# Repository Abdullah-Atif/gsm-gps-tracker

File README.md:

# GSM/GPS Live Vehicle Tracker

**ESP32 / ESP32-C3 + NEO-M8N GPS + SIM800L (2G) → MQTT → live web map**

A low-cost live tracker for cars, bikes and EV three-wheelers. The device reads its position from a NEO-M8N GPS module and sends it over 2G GPRS (SIM800L) every 5 seconds. A static web page shows it live on a map.

The whole system runs with **no server, no PC and no paid service**:

- The device publishes to a free public MQTT broker.
- The map page is a single HTML file on GitHub Pages.
- It subscribes to the same broker over a secure WebSocket.

**Live map:** <https://abdullah-atif.github.io/gps-tracker/#key=YOUR_TRACKER_KEY>

Author: **Abdullah Atif**, Department of EEE, BUET.

---

## Contents

- [How it works](#how-it-works)
- [Hardware](#hardware)
- [Repository layout](#repository-layout)
- [Quick start](#quick-start)
- [Wiring](#wiring)
- [Carrier PCBs](#carrier-pcbs)
- [Data format](#data-format)
- [Design decisions](#design-decisions)
- [Troubleshooting](#troubleshooting)
- [Project status](#project-status)
- [Security note](#security-note)
- [License](#license)

---

## How it works

```mermaid
flowchart LR
    GPS["NEO-M8N GPS<br/>NMEA @ 9600 baud"] -->|UART| MCU["ESP32 / ESP32-C3<br/>TinyGPSPlus parser"]
    MCU -->|"UART + AT commands<br/>(TinyGSM)"| GSM["SIM800L<br/>2G GPRS"]
    GSM -->|"MQTT over TCP :1883<br/>(PubSubClient)"| BROKER[("broker.emqx.io<br/>free public MQTT broker")]
    BROKER -->|"MQTT over WebSocket<br/>wss :8084"| WEB["Web map (GitHub Pages)<br/>Leaflet + OpenStreetMap + MQTT.js"]
    WEB --> USER(["Any phone or PC browser"])
```

1. **Read the position.** The ESP32 parses NMEA sentences from the GPS: position, speed, course, altitude, satellites and HDOP.
2. **Connect.** The SIM800L brings up GPRS. Then the ESP32 opens an MQTT connection on plain TCP port 1883. The SIM800L's built-in TLS is too old for modern servers, so plain MQTT is the reliable choice.
3. **Publish.** Every 5 s the device publishes a JSON message as a **retained** message. A page opened later still shows the last known position immediately.
4. **Online/offline status.** The device registers an MQTT **Last Will** (`offline`). If the device loses power or network, the broker publishes it automatically, and the map shows the tracker as offline.
5. **Show the map.** The web page subscribes to `gpstrk/<TRACKER_KEY>/+/loc` and `/status`. It:
   - draws a heading arrow for each device
   - keeps a trail in the browser
   - shows speed, satellites, HDOP and battery voltage.

---

## Hardware

| Part | Notes |
|---|---|
| ESP32 DOIT DevKit V1 (30-pin) **or** ESP32-C3 Super Mini | The DevKit version is tested end to end. The C3 version is a smaller board. |
| NEO-M8N GPS module + patch antenna | 9600 baud default. The antenna must see the sky. |
| SIM800L mini module + antenna | 2G only. Needs a SIM with a data plan and 2G coverage. |
| 1S Li-ion cell (18650 / LiPo, protected) | Powers the SIM800L directly (3.4–4.4 V). |
| MT3608 boost module | 1S cell → 5.0 V for the ESP32 and GPS. |
| 1000 µF + 100 nF capacitors | Next to SIM800L VCC, to absorb the 2 A transmit bursts. |
| 10 kΩ + 20 kΩ resistors | Level divider: ESP32 TX (3.3 V) → SIM800L RXD (2.8 V logic). |
| Slide switch, JST-XH connector | Power switch and battery plug. |

---

## Repository layout

```
gsm-gps-tracker/
├── esp32_devkit/                ESP32 DevKit V1 version (tested)
│   ├── gps_test/                  GPS check with baud-rate auto-detect
│   ├── sim800l_test/              7 PASS/FAIL checks: power, SIM, signal, GPRS, broker TCP
│   ├── sim800l_autodetect/        finds TX/RX orientation + baud, saves 9600 baud in the modem
│   ├── mqtt_sim800l_tracker/      THE TRACKER (2G GPRS)
│   ├── mqtt_wifi_tracker/         same tracker over Wi-Fi / phone hotspot (with network diagnostics)
│   └── pcb/                       KiCad carrier board (60 x 52 mm), Gerbers, BOM, generator
├── esp32c3_supermini/           ESP32-C3 Super Mini version
│   ├── c3_gps_test/
│   ├── c3_sim800l_autodetect/
│   ├── c3_mqtt_sim800l_tracker/   tracker + battery voltage report
│   ├── c3_wiring_diagram.png/.svg full wiring diagram
│   ├── c3_supermini_pinout.png    top/bottom pinout of the Super Mini
│   └── pcb/                       KiCad carrier board v2 (53 x 52 mm), all modules plug in
├── web/index.html               live map page (single file, no build step)
├── LICENSE
└── README.md
```

Each PCB folder has its own README with ordering and assembly notes.

---

## Quick start

### 1. Arduino IDE

1. Install the **esp32 by Espressif Systems** board package.
2. Install these libraries from Library Manager:

| Library | Author |
|---|---|
| TinyGPSPlus | Mikal Hart |
| TinyGSM | Volodymyr Shymanskyy |
| PubSubClient | Nick O'Leary |

3. Pick the board settings:

| Version | Board | Extra setting |
|---|---|---|
| DevKit | **ESP32 Dev Module** | - |
| C3 Super Mini | **ESP32C3 Dev Module** | **Tools → USB CDC On Boot → Enabled** (required for the Serial Monitor) |

### 2. Run the sketches in order

| Step | DevKit sketch | C3 sketch | What to look for |
|---|---|---|---|
| 1 | `gps_test` | `c3_gps_test` | Satellites > 0 and a fix outdoors (first fix can take 1–5 min) |
| 2 | `sim800l_test` | - | All 7 checks PASS |
| 2b | `sim800l_autodetect` | `c3_sim800l_autodetect` | `FOUND` with the right TX/RX orientation; modem saved at 9600 baud |
| 3 | `mqtt_sim800l_tracker` | `c3_mqtt_sim800l_tracker` | `published` lines in the Serial Monitor |

### 3. Configure the tracker

At the top of the tracker sketch:

```cpp
const char APN[]         = "gpinternet";             // Grameenphone; Robi/Airtel "internet", Banglalink "blweb"
const char* TRACKER_KEY  = "change-this-secret-key"; // long random text, also used in the map link
const char* DEVICE_ID    = "car-01";                 // one ID per vehicle
```

### 4. Open the map

```
https://abdullah-atif.github.io/gps-tracker/#key=YOUR_TRACKER_KEY
```

You can also open `web/index.html` from disk or host it yourself. Anyone with the link, key included, can watch the tracker. Several devices with the same key appear on the same map.

---

## Wiring

### ESP32-C3 Super Mini

| ESP32-C3 pin | Connects to | Firmware define |
|---|---|---|
| 5V | MT3608 OUT+ (5.0 V) | - |
| GND | common GND | - |
| GPIO4 | SIM800L TXD | `MODEM_RX_PIN 4` |
| GPIO3 | 10 kΩ → SIM800L RXD (20 kΩ from RXD to GND) | `MODEM_TX_PIN 3` |
| GPIO2 | SIM800L RST | `MODEM_RST_PIN 2` |
| GPIO1 | GPS TX | `GPS_RX_PIN 1` |
| GPIO0 | GPS RX | `GPS_TX_PIN 0` |
| GPIO8 | on-board LED (active LOW), blinks on each publish | `LED_PIN 8` |

> The Super Mini's pin labels are printed on its **underside**. Seen from the top (chip side up, USB-C up), the 5V / GND / 3V3 / GPIO4..0 row is on the **right**. See [`c3_supermini_pinout.png`](esp32c3_supermini/c3_supermini_pinout.png).

### ESP32 DevKit V1

| ESP32 pin | Connects to | Notes |
|---|---|---|
| GPIO16 (RX2) | GPS TX | |
| GPIO17 (TX2) | GPS RX | |
| VIN (5 V) | GPS VCC | from the MT3608 5.0 V output |
| GPIO26 | SIM800L TXD | direct |
| GPIO27 | SIM800L RXD | through the 10k/20k divider |
| GPIO5 | SIM800L RST | optional |
| GND | common GND | |

### Power (both versions)

```
1S Li-ion ─ switch ─ VBAT ─┬─ SIM800L VCC   (1000 µF + 100 nF right at the module)
                           └─ MT3608 IN+ ─ 5.0 V ─┬─ ESP32 5V / VIN  (100 µF)
                                                  └─ GPS VCC
```

- **Never power the SIM800L from the ESP32's 3.3 V or 5 V pin.** It draws up to 2 A in short bursts.
- **Set the MT3608 to 5.0 V with a multimeter before connecting anything.** New modules often ship at 12 V or more.
- The C3 Super Mini has no protection between USB 5 V and its 5V pin. Switch the battery off while USB is plugged in.

---

## Carrier PCBs

Both boards are 2-layer, through-hole only, and generated by Python scripts using the KiCad 7 `pcbnew` API. Each folder contains:

- the `.kicad_pcb` file
- Gerbers (ready for JLCPCB / PCBWay)
- BOM, DRC report and renders.

Altium users: **File → Import Wizard → KiCad Design Files**, then repour the polygons.

| ESP32-C3 Super Mini carrier v2 (53 x 52 mm) | ESP32 DevKit carrier v1 (60 x 52 mm) |
|---|---|
|  |  |
| Every module plugs into sockets on **all** of its pins. ESP32-C3 and GPS on top; SIM800L and MT3608 underneath. | DevKit, SIM800L and power parts on the board; GPS on a 4-pin cable header. |

Before ordering, read the "Check before ordering" list in each PCB README. The module footprints of the C3 board were estimated from the real modules and must be checked against yours:

- SIM800L row spacing (two footprint options are provided)
- GPS header order
- Super Mini pin labels

---

## Data format

| Topic | Payload | Retained |
|---|---|---|
| `gpstrk/<TRACKER_KEY>/<DEVICE_ID>/loc` | JSON position (below) | yes |
| `gpstrk/<TRACKER_KEY>/<DEVICE_ID>/status` | `online` / `offline`; `offline` is the MQTT Last Will | yes |

```json
{
  "device_id": "car-01",
  "fix": true,
  "lat": 23.810331,
  "lng": 90.412521,
  "speed_kmh": 18.52,
  "course": 274.3,
  "alt_m": 14.2,
  "sats": 9,
  "hdop": 0.98,
  "batt_mv": 3987,
  "gps_time": "2026-10-06T10:15:42Z"
}
```

Fields are sent only when valid. `batt_mv` is measured by the SIM800L and reported by the C3 firmware.

---

## Design decisions

| Option | Result |
|---|---|
| Own HTTP server on a PC + tunnel | Works, but the PC must stay on. Rejected for a vehicle. |
| Free cloud hosts | Force HTTPS, which the SIM800L cannot do reliably, or need a credit card, or have idle shutdowns and request limits. |
| **Public MQTT broker + static page on GitHub Pages** | **Chosen.** The SIM800L speaks plain MQTT on 1883 and the browser uses secure WebSocket on 8084. No server to maintain, free, and a retained message plus Last Will give "last known position" and online/offline status for free. |

---

## Troubleshooting

| Symptom | Cause / fix |
|---|---|
| SIM800L resets, LED blinks fast forever, no network | Power. It needs 2 A peaks: short thick wires, 1000 µF at VCC, common GND. |
| Garbage characters or no `OK` from the SIM800L | Wrong baud rate or swapped TX/RX. Run `sim800l_autodetect`; it tests both orientations and all common bauds. |
| Module answers calls but the ESP32 gets nothing | Same as above. Also check that the divider is on the **RXD** line, not TXD. |
| Wi-Fi hotspot connected but no internet on the ESP32 | Many Bangladeshi mobile networks hand out IPv6 only. Set the phone's APN protocol to **IPv4/IPv6**. Not an issue with the SIM800L. |
| Position 30–70 m off | Poor sky view (HDOP > 5, about 4 satellites). Outdoors with 8+ satellites and HDOP < 2 gives about 2–5 m. |
| Map shows "waiting for data" | Device online but no fresh fix yet, or the key in the link does not match `TRACKER_KEY`. |
| ESP32-C3 shows nothing in the Serial Monitor | Enable **USB CDC On Boot**. |

---

## Project status

- [x] GPS test and baud auto-detect
- [x] SIM800L test and orientation/baud auto-detect
- [x] Live tracking over 2G (ESP32 DevKit + SIM800L), verified on the live map
- [x] Wi-Fi / hotspot variant with network diagnostics
- [x] Web map: multiple devices, trail, online/offline, speed, satellites, HDOP, battery
- [x] ESP32-C3 Super Mini firmware and carrier PCB v2 design
- [ ] ESP32-C3 firmware tested on hardware
- [ ] Carrier PCBs fabricated and tested
- [ ] Optional: LoRa variant for SIM-free tracking in a limited area

---

## Security note

The MQTT broker is public. The only secret is `TRACKER_KEY`, which is part of the topic name:

- Use a long random key.
- Share the map link only with people who should see the vehicle.

This is a hobby/student project. Do not rely on it for safety-critical or anti-theft use.

---

## License

[MIT](LICENSE) © 2026 Abdullah Atif

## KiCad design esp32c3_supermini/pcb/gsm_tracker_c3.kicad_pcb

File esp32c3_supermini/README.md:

# GSM/GPS Tracker: ESP32-C3 Super Mini version

This version replaces the ESP32 DevKit with the much smaller **ESP32-C3 Super Mini** (22.5 x 18 mm). It uses the same MQTT broker, topics, JSON format and web page as the DevKit version, so the map at `https://abdullah-atif.github.io/gps-tracker/#key=...` works unchanged.

## Folder contents

| Folder | Purpose |
|---|---|
| `c3_gps_test/` | Checks the GPS on the C3 pins |
| `c3_sim800l_autodetect/` | Checks SIM800L wiring and baud rate, then fixes the modem at 9600 baud |
| `c3_mqtt_sim800l_tracker/` | The tracker firmware |
| `pcb/` | KiCad 7 board, Gerbers, BOM, renders and generator script |

Run the sketches in this order: GPS test → SIM800L autodetect → tracker.

## Arduino IDE settings (important)

| Setting | Value |
|---|---|
| Board | **ESP32C3 Dev Module** |
| Tools → USB CDC On Boot | **Enabled** (otherwise there is no Serial Monitor over USB, and UART0 is taken) |
| Libraries | TinyGPSPlus, TinyGSM, PubSubClient |

The ESP32-C3 has only two hardware UARTs:

- **UART0** (`HardwareSerial(0)`) is used for the GPS.
- **UART1** is used for the SIM800L.
- The Serial Monitor runs over native USB.

## Wiring diagram

`c3_wiring_diagram.svg` is the same diagram as a vector file. `make_wiring_diagram.py` regenerates both: `python3 make_wiring_diagram.py c3_wiring_diagram.svg c3_wiring_diagram.png`.

## Pin map (PCB v2)

The pin labels are printed on the **underside** of the Super Mini. Seen from the top (chip side up, USB-C up), the 5V / GND / 3V3 / GPIO4..0 row is on the **right**. Flip the board and it is on the left. All signals use this row; the other row (GPIO5..10, 20, 21) only holds the board mechanically.

| Super Mini pin | Connected to | Firmware define |
|---|---|---|
| 5V | MT3608 boost output (5.0 V) | - |
| GND | GND | - |
| GPIO4 | SIM800L TXD | `MODEM_RX_PIN 4` |
| GPIO3 | SIM800L RXD, through the 10k/20k divider (2.8 V logic) | `MODEM_TX_PIN 3` |
| GPIO2 | SIM800L RST (strapping pin; the SIM800L pull-up keeps it high at boot) | `MODEM_RST_PIN 2` |
| GPIO1 | GPS TX | `GPS_RX_PIN 1` |
| GPIO0 | GPS RX | `GPS_TX_PIN 0` |
| GPIO8 | On-board blue LED (active LOW; blinks on every published report) | `LED_PIN 8` |

> PCB v1 had GPIO3/GPIO4 the other way round. The sketches in this folder are already set for v2. If you hand-wire a v1 board, swap `MODEM_RX_PIN` and `MODEM_TX_PIN`, or just run `c3_sim800l_autodetect`, which finds the orientation by itself.

## Carrier PCB v2 (`pcb/`)

Every module plugs straight into the board. Nothing hangs on jumper wires. Each module sits in female sockets that take **all** of its pins, unused ones included, so it is held on both sides.

- 2 layers, **53 x 52 mm**.
- **Front side:**

  | Part | Mounting |
  |---|---|
  | ESP32-C3 Super Mini | 2 x 1x8 sockets, **chip side up**, USB-C at the top edge. J5 (right) = 5V/GND/3V3/4..0 row, J6 (left) = GPIO5..21 row |
  | NEO-M8N GPS board | 1x4 socket J4; the board lies flat over the lower half |
  | Power parts | JST battery connector J1, slide switch SW1, 1000 µF + 100 nF (SIM800L), 100 µF (5 V), 10k/20k divider |

- **Back side:**

  | Part | Mounting |
  |---|---|
  | SIM800L mini | Interface row (GND TXD RXD RST VCC NET) in J3. Audio row (RING DTR MIC SPK, no connection) in J8 **or** J9 |
  | MT3608 boost module | Lies flat, connected by its 4 pads |

- Power path:

  ```
  1S Li-ion → SW1 → VBAT → SIM800L
                         → MT3608 → 5 V → C3 5V pin + GPS VCC
  ```

- Design rule check: **0 unconnected items.** The only error is the intended J8/J9 courtyard overlap, because they are two alternative positions and only one gets fitted. The remaining warnings are cosmetic: silkscreen overlap and library-link notices.
- **Altium:** File → Import Wizard → KiCad Design Files → `gsm_tracker_c3.kicad_pcb`, then repour the polygons.
- **Fabrication:** upload `gsm_tracker_c3_gerbers.zip` to JLCPCB or PCBWay.

### Assembly

1. **MT3608 first.** Set it to **5.0 V** on the bench, then solder it flat on the back. Use short wire legs or cut component leads through its IN+/IN-/OUT+/OUT- holes.
2. **Back sockets.** Solder J3 and either J8 or J9 on the back, from the front side.
3. **Front parts.** Solder J5, J6, J4 and the rest of the front parts.
4. **SIM800L.** Plug it in from the back. Its component side faces away from the board and the antenna end points down, as printed on the back silkscreen.
5. **GPS board.** Plug it into J4. Stick a foam pad (about 11 mm, or stacked foam tape) or a nylon spacer under its far end so it lies level. Place the patch antenna on top, facing the sky.
6. **Standoffs.** Mount the board on **15 mm or taller** standoffs (M2, holes H1/H2), because the SIM800L hangs under it.

### Check before ordering (dimensions were estimated from the breadboard photo)

1. **SIM800L orientation.** Hold the module component side up with the antenna end towards you. The interface row (NET VCC RST RXD TXD GND) must be on the **right**, with **NET nearest the antenna end**. If your module is mirrored, tell me and I will flip the footprint.
2. **SIM800L row spacing.** Measure from the centre of a pin in one row to the centre of the facing pin in the other row:
   - about **17.8 mm**: fit **J8**
   - about **20.3 mm**: fit **J9**
   - any other value: send me the measurement.
3. **GPS header order.** With the header on the left and the board body to the right, the pins from top to bottom must read **GND, TX, RX, VCC**. Check the labels printed on your GPS board.
4. **GPS board size.** The board assumes about 36 x 26 mm (dashed outline on the front silkscreen). A slightly larger board is fine, because it sits above the other parts.
5. **Super Mini pin order.** Turn your board over and read the printed labels with USB-C at the top. They must read:
   - Left row (bottom view): 5V, G, 3.3, 4, 3, 2, 1, 0
   - Right row (bottom view): 5, 6, 7, 8, 9, 10, 20, 21

   This is the common layout. If your labels differ, do not use this PCB as is.
6. **Battery.** Use a protected cell and charge it outside the board. The firmware reports the cell voltage (`batt_mv`), measured by the SIM800L, in every message.

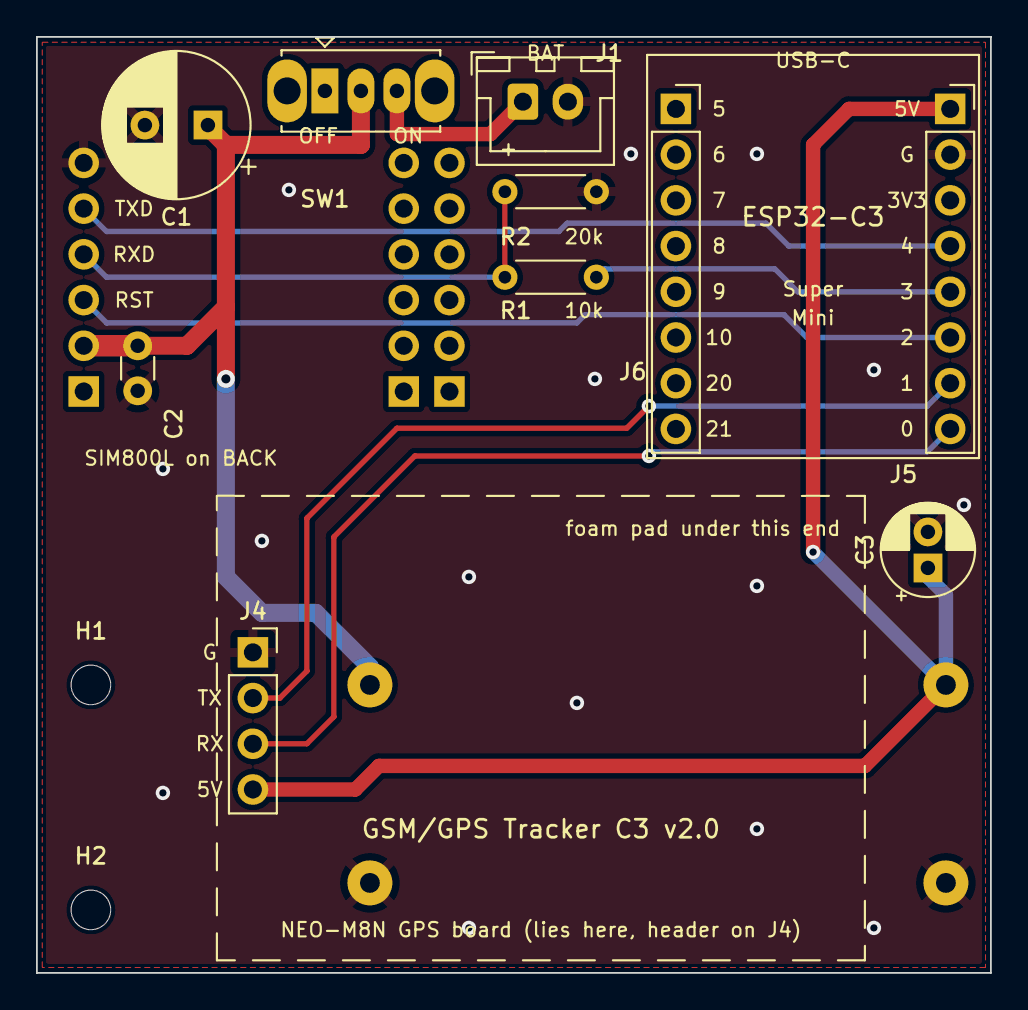
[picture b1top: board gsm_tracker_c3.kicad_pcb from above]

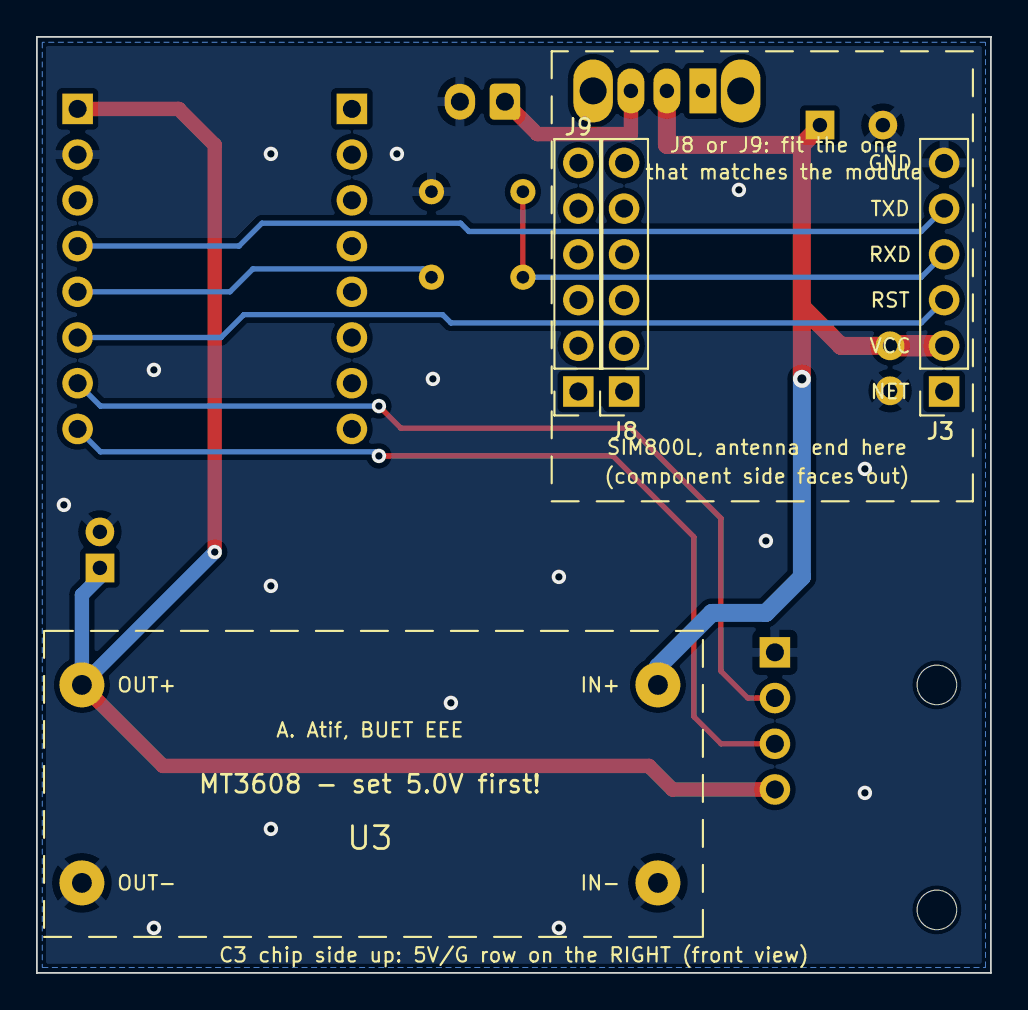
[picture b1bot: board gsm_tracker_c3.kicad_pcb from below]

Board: 2 copper layers, 53.0 x 52.0 mm, 16 parts (3 on the bottom side), 10 nets.

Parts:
C1: 1000uF_10V; CP_Radial_D8.0mm_P3.50mm
C2: 100nF; C_Disc_D3.0mm_W1.6mm_P2.50mm
C3: 100uF_10V; CP_Radial_D5.0mm_P2.00mm
H1, H2: M2; MountingHole_2.2mm_M2
J1: BATT_1S; JST_XH_B2B-XH-A_1x02_P2.50mm_Vertical
J3: SIM800L_IF; PinSocket_1x06_P2.54mm_Vertical
J4: GPS; PinSocket_1x04_P2.54mm_Vertical
J5: C3_POWER_ROW; PinSocket_1x08_P2.54mm_Vertical
J6: C3_GPIO5_21_ROW; PinSocket_1x08_P2.54mm_Vertical
J8: SIM800L_AUDIO_17.78; PinSocket_1x06_P2.54mm_Vertical
J9: SIM800L_AUDIO_20.32; PinSocket_1x06_P2.54mm_Vertical
R1: 10k; R_Axial_DIN0204_L3.6mm_D1.6mm_P5.08mm_Horizontal
R2: 20k; R_Axial_DIN0204_L3.6mm_D1.6mm_P5.08mm_Horizontal
SW1: PWR; SW_Slide_SPDT_Straight_CK_OS102011MS2Q
U3: MT3608_5V

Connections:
+5V: C3.1, J4.4, J5.1, U3.3
ESP_TX_SIM: J5.5, R1.2
GND: C1.2, C2.2, C3.2, J1.2, J3.6, J4.1, J5.2, R2.2, U3.2, U3.4
GPS_RX: J4.3, J5.8
GPS_TX: J4.2, J5.7
SIM_RST: J3.3, J5.6
SIM_RXD: J3.4, R1.1, R2.1
SIM_TXD: J3.5, J5.4
VBAT: C1.1, C2.1, J3.2, SW1.2, U3.1
VBAT_RAW: J1.1, SW1.3

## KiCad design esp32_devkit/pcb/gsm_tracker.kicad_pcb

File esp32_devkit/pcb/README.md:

# GSM/GPS Tracker carrier board v1.0

A compact 2-layer carrier PCB (**60 x 52 mm**) for the working tracker. The ESP32 DevKit, SIM800L module and NEO-M8N GPS plug into headers, so there is no loose wiring and no SMD soldering.

## Files

| File | Purpose |
|---|---|
| `gsm_tracker.kicad_pcb` / `.kicad_pro` | KiCad 7 board (open in KiCad, or import into Altium) |
| `gsm_tracker_gerbers.zip` | Gerber + drill files, ready to upload to JLCPCB / PCBWay |
| `BOM.csv` | Parts list |
| `generate_pcb.py` | Script that generates the board (re-run after changing positions) |
| `drc_report.txt` | KiCad design-rule check report |
| `renders/front.png`, `renders/back.png` | Copper + silkscreen views (back view is mirrored) |

## Opening in Altium Designer

1. Go to **File → Import Wizard → KiCad Design Files**.
2. Select `gsm_tracker.kicad_pcb`.
3. The board imports with its footprints, tracks, nets and copper pours.
4. After importing, run **Tools → Polygon Pours → Repour All**.

## Circuit

```
Li-ion 1S (J1) --SW1--> VBAT --+--> SIM800L VCC   (C1 1000 uF + C2 100 nF at the module)
                               +--> MT3608 IN+ --> 5.0 V --+--> ESP32 VIN  (C3 100 uF)
                                                           +--> GPS 5V (J4)
```

| Signal | ESP32 pin | Module pin | Notes |
|---|---|---|---|
| SIM_TXD | D26 (GPIO26) | SIM800L TXD | direct |
| SIM_RXD | D27 (GPIO27) | SIM800L RXD | 10k / 20k divider (R1, R2) |
| SIM_RST | D5 (GPIO5) | SIM800L RST | direct |
| GPS_TX | RX2 (GPIO16) | GPS TX | |
| GPS_RX | TX2 (GPIO17) | GPS RX | |

These are the same pins the firmware already uses, so no firmware change is needed.

## Before ordering and assembling: please check

1. **ESP32 row spacing.** Measure the distance between the two pin rows of your DevKit.
   - **22.86 mm (0.9 in):** fit header **J6**.
   - **25.40 mm (1.0 in):** fit header **J7** instead.

   Both footprints are on the board. The J6/J7 courtyard overlap in the DRC report is intentional.
2. **SIM800L pin order.** The module must sit so that its pins match the silkscreen labels: NET, VCC, RST, RXD, TXD, GND, from top to bottom.
3. **MT3608 boost module.** This needs extra care:
   - It mounts on the **back**, under the ESP32. Its four pads (IN+, IN−, OUT+, OUT−) are large, so you can fit the module directly with pins or with short wires.
   - Adjust it to **5.0 V with a multimeter before connecting it.** These modules often ship set to 12 V or more, which would destroy the ESP32.
4. **Battery.** Use a protected 18650 cell and charge it outside the board (for example with a TP4056 module that has protection).
   - SIM800L needs at least about 3.4 V, so it may reset when the cell is nearly empty.
   - Pin 1 of J1 is **+**.
5. **GPS.** Connect it through J4 with a short cable and place the GPS antenna facing the sky. Keep it away from the SIM800L antenna.

## Design notes

- The board is 2 layers with GND pours on both sides and stitching vias.
- Track widths:
  - VBAT: 1.0–1.2 mm (SIM800L draws 2 A peaks)
  - 5 V: 0.8 mm
  - signals: 0.3 mm
- Minimum clearance is 0.2 mm, and vias are 0.8/0.4 mm. Both are inside standard JLCPCB/PCBWay capabilities.
- There is a copper keep-out under the ESP32 PCB antenna.
- DRC result:
  - **0 unconnected items.**
  - The only reported error is the intentional J6/J7 courtyard overlap.
  - The remaining warnings are cosmetic: silkscreen overlaps and library-link notices.

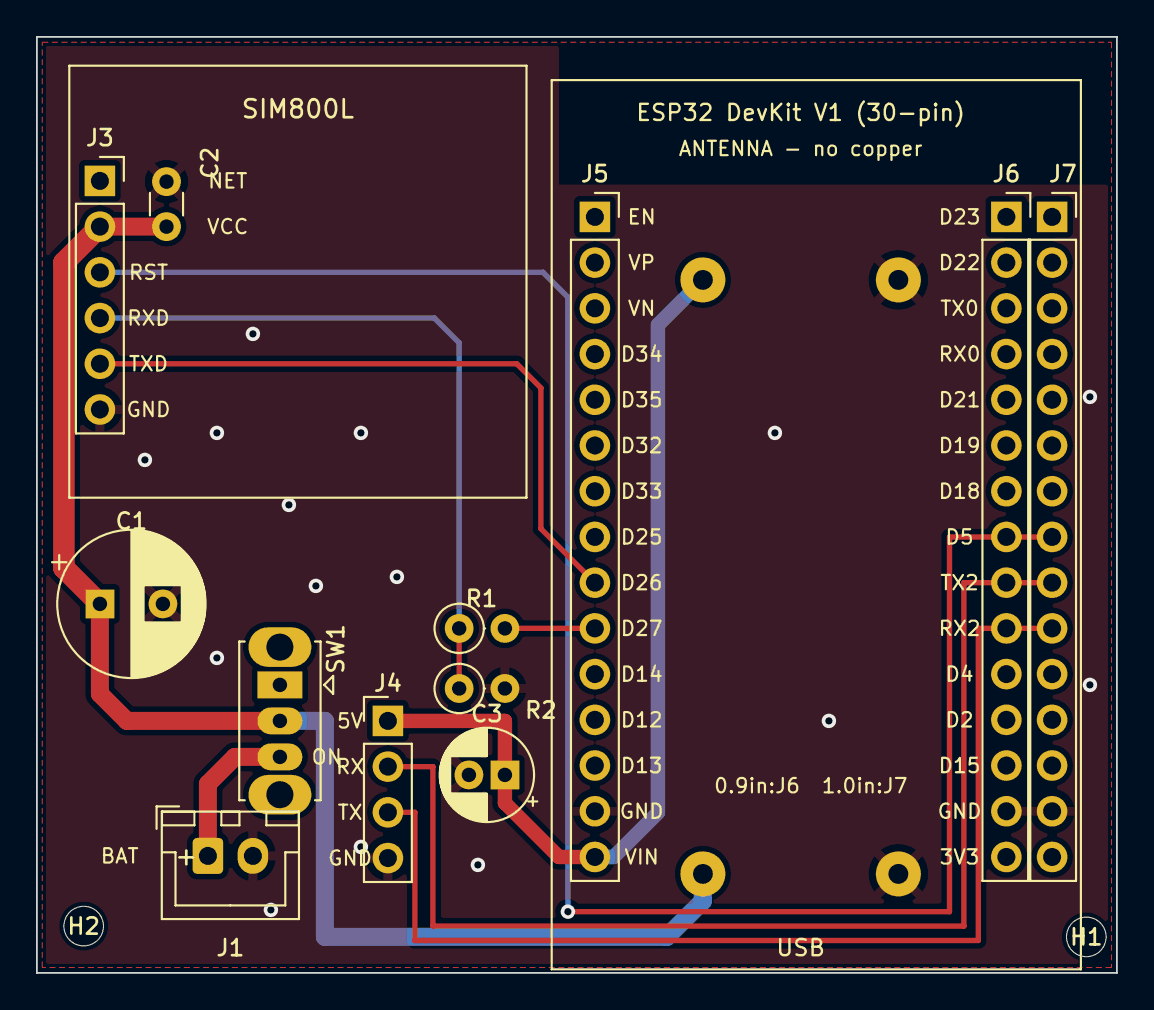
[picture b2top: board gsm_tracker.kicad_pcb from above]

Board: 2 copper layers, 60.0 x 52.0 mm, 15 parts (0 on the bottom side), 10 nets.

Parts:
C1: 1000uF_10V; CP_Radial_D8.0mm_P3.50mm
C2: 100nF; C_Disc_D3.0mm_W1.6mm_P2.50mm
C3: 100uF_10V; CP_Radial_D5.0mm_P2.00mm
H1, H2: M2; MountingHole_2.2mm_M2
J1: BATT_1S; JST_XH_B2B-XH-A_1x02_P2.50mm_Vertical
J3: SIM800L; PinSocket_1x06_P2.54mm_Vertical
J4: GPS; PinHeader_1x04_P2.54mm_Vertical
J5: ESP32_L; PinSocket_1x15_P2.54mm_Vertical
J6: ESP32_R_0.9in; PinSocket_1x15_P2.54mm_Vertical
J7: ESP32_R_1.0in_ALT; PinSocket_1x15_P2.54mm_Vertical
R1: 10k; R_Axial_DIN0207_L6.3mm_D2.5mm_P2.54mm_Vertical
R2: 20k; R_Axial_DIN0207_L6.3mm_D2.5mm_P2.54mm_Vertical
SW1: PWR; SW_Slide_SPDT_Straight_CK_OS102011MS2Q
U3: MT3608_5V

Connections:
+5V: C3.1, J4.1, J5.15, U3.3
ESP_IO27: J5.10, R1.2
GND: C1.2, C2.2, C3.2, J1.2, J3.6, J4.4, J5.14, J6.14, J7.14, R2.2, U3.2, U3.4
GPS_RX: J4.2, J6.9, J7.9
GPS_TX: J4.3, J6.10, J7.10
SIM_RST: J3.3, J6.8, J7.8
SIM_RXD: J3.4, R1.1, R2.1
SIM_TXD: J3.5, J5.9
VBAT: C1.1, C2.1, J3.2, SW1.2, U3.1
VBAT_RAW: J1.1, SW1.3

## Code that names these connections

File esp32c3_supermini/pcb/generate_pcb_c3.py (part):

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The left row (GPIO5..10, 20, 21) is only mechanical support.

Firmware for this board: MODEM_RX_PIN 4, MODEM_TX_PIN 3, MODEM_RST_PIN 2,
                         GPS_RX_PIN 1, GPS_TX_PIN 0.

Module footprints were estimated from a breadboard photo (not measured).
Check the assumptions listed in README.md before ordering.
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# The lanes pass between the pads of the left C3 row (J6) to reach the right row (J5).
track([(SIM_X, SIM_Y["TXD"]), (3.87, 10.81), (29.0, 10.81), (29.46, 10.35), (40.5, 10.35),
       (41.77, c3_y(4)), (C3_R_X, c3_y(4))],
      "SIM_TXD", SIG, B)                                                   # TXD -> GPIO4
track([(SIM_X, SIM_Y["RXD"]), (3.87, R1_Y), (R_X1, R1_Y)], "SIM_RXD", SIG, B)   # RXD -> R1
track([(R_X1, R2_Y), (R_X1, R1_Y)], "SIM_RXD", SIG, F)                     # R2 -> divider node
track([(R_X2, R1_Y), (31.54, 12.89), (41.0, 12.89), (42.27, c3_y(5)), (C3_R_X, c3_y(5))],
      "ESP_TX_SIM", SIG, B)                                                # R1 -> GPIO3
track([(SIM_X, SIM_Y["RST"]), (3.87, 15.89), (30.0, 15.89), (30.46, 15.43), (41.5, 15.43),
       (42.77, c3_y(6)), (C3_R_X, c3_y(6))],
      "SIM_RST", SIG, B)                                                   # RST -> GPIO2

# GPS signals (front)
track([(C3_R_X, c3_y(7)), (49.47, 20.51), (34.0, 20.51)], "GPS_TX", SIG, B)  # back, between J6 pads
via(34.0, 20.51, "GPS_TX")
track([(34.0, 20.51), (32.77, 21.74), (20.0, 21.74), (15.0, 26.74), (15.0, 35.23),
       (13.5, GPS_Y["TX"]), (GPS_X, GPS_Y["TX"])], "GPS_TX", SIG, F)      # GPS TX -> GPIO1
track([(C3_R_X, c3_y(8)), (49.47, 23.05), (34.23, 23.05), (34.0, 23.28)], "GPS_RX", SIG, B)  # back, below J6
via(34.0, 23.28, "GPS_RX")
track([(34.0, 23.28), (21.0, 23.28), (16.5, 27.78), (16.5, 37.77),
       (15.0, GPS_Y["RX"]), (GPS_X, GPS_Y["RX"])], "GPS_RX", SIG, F)      # GPIO0 -> GPS RX

# GND stitching vias
for x, y in [(14.0, 8.5), (33.0, 6.5), (40.0, 6.5), (46.5, 18.5), (31.0, 19.0),
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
